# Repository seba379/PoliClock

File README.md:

# PoliClock

**Orologio da scrivania alimentato via USB, integrato nel volto di una poliziotta chibi stampata in 3D.**

> Stato: **specifiche preliminari (v0.6), schema e PCB KiCad rev 0.2 in bozza, non validati né ordinati** · Aggiornamento: 2026-11-08\
> Lingua progetto: italiano · Documentazione in Markdown · Hardware non ancora acquistato né validato.

## Il prodotto

PoliClock è un regalo personalizzato: una statuetta simpatica e stilizzata di una poliziotta, con un display **circolare integrato al posto del volto**. Durante il giorno il quadrante visualizza **ora, data, temperatura ambiente e umidità relativa**; di notte si spegne. È alimentato in continuo da un **cavo USB-C** collegato al retro della base d'appoggio, che contiene la scheda (`DEC-048`); nella V1 non c'è batteria.

La modalità scelta è **ibrida**: quadrante normalmente attenuato ma leggibile; la pressione di un pulsante attiva temporaneamente la luminosità elevata. La priorità è la qualità estetica senza sacrificare sicurezza, affidabilità e manutenzione.

## Decisioni già confermate

- Statuetta **poliziotta chibi**, volutamente sproporzionata, da stampare in 3D.
- Display **rotondo**, montato a filo/in incasso al posto del viso; non esterno o incollato.
- Schermata V1: **ora, data, temperatura e umidità**; niente funzioni domotiche o statistiche richieste.
- **Nessuna batteria nella V1**: alimentazione continua da **cavo USB-C** sulla parte posteriore bassa, sul retro della base d'appoggio che contiene la scheda (`DEC-048`). Eventuale batteria rimandata a versioni future.
- Schermo **attenuato in condizioni normali**, più luminoso dopo un'interazione.
- **Di notte il display è spento** (default 23:00–07:00, configurabile).
- Aspetto con **uniforme blu e cappello**.
- **Nessun Wi-Fi/NTP nella V1**: l'ora si imposta offline.
- Elettronica su **PCB custom** (KiCad, prodotto e assemblato da JLCPCB): scheda principale separata dal display, collegata via cavo.
- Strumenti: **KiCad 10**, **VS Code + ESP-IDF**, **Blender** e CAD a codice (build123d).
- Display **IPS rotondo 1,28"** (240×240, GC9A01) e interazione con un **pulsante** fisico; display su **modulo a 7 pin** provabile su breadboard, senza touch (`DEC-034`).
- Impostazioni (ora, fascia notte) da un **configuratore su PC** collegato via USB.

## Architettura candidata, NON ancora congelata

- **Scheda principale** rettangolare (busto/base preferito, posizione da confermare con il CAD): modulo **ESP32-C3-WROOM-02-N4** (`DEC-044`), protezioni USB, regolatore 3,3 V, USB-C, connettori.
- **RTC esterno** su modulo Adafruit DS3231 STEMMA QT con pila CR1220, collegato via cavo: l'ora resta salva a cavo scollegato.
- **Modulo display** GC9A01 nella testa, collegato alla scheda principale con un cavetto a 7 fili attraverso il collo.
- Sensore T/RH: **Sensirion SHT40** su modulo breakout commerciale, in vano ventilato, collegato con 4 fili.
- Prima del PCB: **prototipo su banco** con moduli commerciali per validare display su cavo, consumi e firmware.
- Firmware **ESP-IDF**.

**Importante:** consumi, temperature interne e ingombri vanno misurati sul prototipo prima di consolidare la BOM.

| Concept del prodotto | Schema a blocchi |
|---|---|
|  |  |

Le immagini sono **illustrative** (vedi [assets](assets/README.md)).

## Documentazione

| Documento | Contenuto |
|---|---|
| [Visione e perimetro](docs/00-visione-perimetro.md) | Scopo, utenti, esclusioni, vincoli |
| [Requisiti di prodotto](docs/01-requisiti-prodotto.md) | Requisiti identificati, criteri di accettazione |
| [Architettura hardware](docs/02-architettura-hardware.md) | Moduli, collegamenti, selezione candidata |
| [Alimentazione](docs/03-alimentazione-ricarica.md) | USB-C, regolatore, tampone RTC, consumi e calore |
| [Specifiche firmware](docs/04-specifiche-firmware.md) | Componenti, stati, timekeeping, errori |
| [UI/UX](docs/05-interfaccia-utente.md) | Layout, luminosità, interazione, messaggi |
| [Progettazione meccanica](docs/06-progettazione-meccanica.md) | Testa, corpo, base con zavorra, stampa 3D |
| [Verifiche e test](docs/07-piano-verifica.md) | Prove funzionali, elettriche e meccaniche |
| [BOM preliminare](docs/08-bom-preliminare.md) | Acquisti, alternative e controlli pre-ordine |
| [Roadmap](docs/09-roadmap.md) | Milestone, deliverable, gate |
| [Decisioni e questioni aperte](docs/10-decisioni-aperte.md) | Decision log e dubbi tecnici |
| [Fonti](docs/11-fonti.md) | Documenti ufficiali e risorse tecniche |
| [Selezione componenti](docs/12-selezione-componenti.md) | Componenti dello schema, codici LCSC, assegnazione GPIO |
| [Preventivo JLCPCB](docs/13-ordine-jlcpcb.md) | File da caricare, opzioni PCB e montaggio, controlli DFM, parti da saldare a mano |
| [Hardware KiCad](hardware/README.md) | Progetti KiCad, PDF, BOM JLCPCB, rigenerazione |

## Organizzazione di lavoro prevista

```text
PoliClock/
├── README.md
├── docs/                  # specifiche e verifiche
├── assets/                # concept, render, modelli di riferimento futuri
├── firmware/              # progetto ESP-IDF da avviare in M1/M4
├── hardware/              # progetto KiCad scheda principale rev 0.2 (bozza), BOM/CPL JLCPCB (M2)
├── tools/                 # configuratore da PC via USB (M4)
└── mechanical/            # Blender (chibi), build123d (parti tecniche), STL/3MF
```

Le directory `firmware/`, `tools/` e `mechanical/` sono **previste**, non ancora presenti: non si pubblicano file placeholder che possano essere scambiati per firmware o modelli funzionanti.

## Convenzioni

- **CONF**: decisione espressamente confermata dall'utente.
- **CAND**: soluzione tecnica candidata, soggetta a verifica.
- **TGT**: obiettivo di progetto non ancora validato.
- **TBD**: scelta/misura ancora da definire.
- Ogni requisito ha un ID stabile (es. `PR-FUN-001`) e uno o più test di accettazione (`VT-...`).
- Nessun dato prestazionale ipotetico va descritto come misurato.

## Primo passo operativo

Milestone M1 della [roadmap](docs/09-roadmap.md): scegliere sui datasheet MCU, RTC e regolatore, montare il **prototipo su banco** con moduli commerciali, provare il display su cavo e misurare i consumi **prima** di disegnare il PCB e il CAD.

## Avvertenze

Progetto hobbistico per un regalo personale, non prodotto certificato per vendita. L'alimentazione continua da USB richiede comunque protezione dell'ingresso, fissaggio dei connettori e verifica termica a scocca chiusa. L'estetica richiama una poliziotta, senza implicare affiliazione o approvazione ufficiale della Polizia di Stato.

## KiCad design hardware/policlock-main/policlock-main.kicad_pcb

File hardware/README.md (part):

# Hardware PoliClock (KiCad 10)

**Stato (rev 0.2, 2026-11-08):** schema e PCB della scheda principale **in bozza**, rifatti dopo la revisione tecnica indipendente (esito sulla rev 0.1: *NOT APPROVED FOR FABRICATION*; stato dei rilievi in [docs/10](../docs/10-decisioni-aperte.md) §6).

**Correzioni del 2026-11-08, ramo `codex/pcb-edge-courtyard-fixes`:** C7 spostato a 2,60 mm dal bordo; courtyard/F.Fab di J2–J5 completati; FID1 spostato di 1,5 mm con la sua zona di rispetto. Commit autorizzato dal proprietario; ERC/DRC e confronto riportati nella [nota delle modifiche](../docs/revisioni/2026-11-08/correzioni/README.md). Vista 2D dei courtyard: [pcb-courtyard.svg](../docs/revisioni/2026-11-08/correzioni/pcb-courtyard.svg).

**Chiusura dei rilievi residui (2026-11-08, [verifica](../docs/revisioni/2026-11-08/verifica-claude.md)):**

- C1 portato a **1 µF** (C15849) e C2 a **4,7 µF** (C19666, Basic): restano 5,7 µF nominali su VBUS (`DEC-042`).
- Cartigli portati a rev 0.2 e annotazioni dello schema corrette.
- `esporta.py` ora si ferma se ERC, DRC o il controllo meccanico falliscono.
- PDF, BOM, layout e render 3D sono rigenerati.

**Pin BUSY su J2 (`DEC-049`, 2026-11-09):**

- J2 diventa un header **1×8** (`PinHeader_1x08_P2.54mm_Horizontal`, simbolo `PoliClock:PinHeader_1x08_P2.54_THT`): pin 1–7 invariati, **pin 8 = BUSY** per un eventuale e-paper.
- Il pin 8 va a IO1 attraverso R23 1 kΩ (C21190, Basic); TP10 resta su IO1. Il pull-down interno lo abilita il firmware.
- J2 si sposta di 2,54 mm a sinistra: con il pin 1 fermo, il pin 8 cadrebbe sotto U3.
- Modifica con `scripts/dec049_schema.py` e `scripts/dec049_pcb.py`, poi `sbroglia_main.py --conserva` e `cucitura_gnd.py`.
- ERC 0, DRC 0/0/0 con parità, controllo meccanico PASS.
- Verifica di IO0/IO1 sui datasheet Espressif in [docs/10](../docs/10-decisioni-aperte.md) §16.
- Dopo la terza revisione (R3-001, R3-003): 8 vie GND in più (4 accanto alla EPAD di U3, 1 vicino al pin 9, 3 nell'isola del retro della zona J2/passivi), aggiunte a mano; DRC 0/0/0. Dettagli in [docs/10](../docs/10-decisioni-aperte.md) §17.

**Contorno rettangolare 50,5 × 41,5 mm (`DEC-045`, 2026-11-08):** niente intaglio, antenna di U3 sulla scheda con zona vietata, corpo di tutte le parti montate da JLC a ≥ 2,5 mm da ogni bordo tranne J1 (unica eccezione DFM). Modifica con `scripts/dec045_pcb.py`. ERC 0, DRC 0/0/0, controllo meccanico PASS (margine minimo 2,99 mm). Dettagli in [docs/10](../docs/10-decisioni-aperte.md) §12.

**Modulo ESP32-C3-WROOM-02-N4 (`DEC-044`, 2026-11-08):** sostituisce il MINI-1-H4X (a JLC solo "Standard"). Impronta di progetto `PoliClock:ESP32-C3-WROOM-02` (derivata da quella di KiCad, EPAD senza vie dopo `DEC-046`, niente serigrafia sopra l'antenna), intaglio allargato a 8,5 × 20,2 mm, coppia USB ridisegnata sui pin 13/14, sbroglio rifatto, cucitura GND, R16 10 k + C11 10 nF (FIN-003), serigrafia a 1,0 mm (FIN-005), regola PTH in `.kicad_dru` (FIN-007), script Gerber bloccato (FIN-006). ERC 0, DRC 0/0/0 con parità, controllo meccanico PASS. Dettagli in [docs/10](../docs/10-decisioni-aperte.md) §11.

**Connettori a foro passante (`DEC-043`, 2026-11-08):** J2 (header 1×7 2,54 mm, 1×8 dal `DEC-049`) e J3/J4/J5 (JST PH B4B-PH-K-S) sono a foro passante e **saldati a mano dal proprietario**, come le 4 linguette del guscio di J1 (`DEC-047`); JLC monta tutto il resto, J1 compreso. Le impronte vengono dalla libreria standard di KiCad 10. J2–J5 hanno il campo `Montaggio` = "a mano, parte del proprietario" e l'attributo "escluso dai file di posizionamento": non compaiono in BOM JLC e CPL, ma sono nella BOM completa. Modifica con `scripts/dec043_connettori_tht.py`, poi sbroglio delle sole connessioni mancanti con `scripts/sbroglia_main.py --conserva`. ERC 0, DRC 0/0/0 con parità, controllo meccanico PASS. Dettagli in [docs/10](../docs/10-decisioni-aperte.md) §10.

- **Report salvati**: ERC e DRC rieseguiti con `kicad-cli` sulla rev 0.2 (`policlock-main/erc.rpt`, `drc.rpt`). Sono verifiche automatiche del progetto.
- **Test eseguiti sull'hardware**: nessuno. Tutti i test del [piano di verifica](../docs/07-piano-verifica.md) sono NOT_RUN.
- **Non ordinare**: prima servono studio volumetrico 1:1 (`OPEN-028`), verifica del modulo display ricevuto (`OPEN-016`), prototipo M1 e DFM JLC. La revisione visiva del proprietario in KiCad è stata fatta il 2026-11-08 con esito positivo (`OPEN-027` chiusa) e ripetuta sul layout finale `09200dc` (`OPEN-030` chiusa).

## Struttura

| Cartella | Contenuto |
|---|---|
| `policlock-main/` | Scheda principale: schema gerarchico (USB e alimentazione, MCU, display a 7 pin, periferiche I²C e pulsante), PCB 50,5 × 41,5 mm, PDF, BOM e CPL per JLCPCB, render, STEP della sagoma, report ERC/DRC |
| `lib/` | Libreria di progetto `PoliClock` (simboli e footprint delle parti specifiche) |
| `scripts/` | Generatori di schema e PCB, sbroglio con Freerouting, esportazioni |

È l'**unico PCB custom**: display, sensore SHT40 e RTC sono moduli commerciali collegati con cavetti (`DEC-024`, `DEC-028`, `DEC-034`).

Ogni componente montato da JLC ha il campo **`LCSC`** (codice JLCPCB/LCSC); J2–J5 non hanno codice LCSC e portano il campo **`Montaggio`** = "a mano, parte del proprietario" (`DEC-043`). Simboli e footprint di passivi, SOT, USBLC6, TLV75533 e AO3401A vengono dalle librerie standard di KiCad 10; la USB-C usa il footprint KiCad ricavato dal disegno HRO (copiato nella libreria di progetto con la serigrafia frontale tolta); anche i connettori a foro passante J2–J5 usano impronte standard (`Connector_PinHeader_2.54mm`, `Connector_JST`); le altre parti vengono dalla libreria `PoliClock`.

## PCB della scheda principale

- `policlock-main/policlock-main.kicad_pcb`: **50,5 × 41,5 mm, 2 strati, 1,6 mm, componenti solo sopra** (`DEC-030`, `DEC-045`). L'antenna del modulo ESP32 sta sulla scheda, verso il bordo destro, sopra una zona vietata senza rame su entrambi gli strati (niente intaglio). Piani GND su entrambi gli strati. Nessun tasto: reset e boot dai punti di test TP6 (EN) e TP11 (IO9) sul retro (`DEC-039`). Tre fiducial da 1 mm sul lato componenti. Dettagli in [docs/02](../docs/02-architettura-hardware.md) §3.2.
- **Regole JLCPCB** (vincolo `SC-008`, `DEC-040`; pagine ufficiali consultate il 2026-11-08, da ricontrollare all'ordine):
  - fabbricazione 2 strati: distanza 0,15 mm, pista ≥ 0,15 mm (alimentazioni 0,3–0,4 mm), anello delle piazzole PTH ≥ 0,18 mm (regola `.kicad_dru`), testi della serigrafia ≥ 1,0 mm, vie 0,6/0,3 mm, foro-foro ≥ 0,25 mm (JLC 0,2), foro-rame ≥ 0,3 mm (JLC 0,28), rame-bordo 0,3 mm (JLC 0,2) più una fascia di 0,45 mm senza piste lungo il contorno;
  - assemblaggio: corpo dei componenti montati da JLC ≥ 2,5 mm da ogni bordo; controllo aggiuntivo `scripts/verifica_meccanica_pcb.py`, richiamato anche dal generatore. **Unica eccezione J1** (USB-C a filo del bordo inferiore), da approvare al DFM JLC (`DEC-045`). Le parti saldate a mano (J2–J5, `DEC-043`) non hanno il margine, ma il loro courtyard è controllato; le regole di fabbricazione valgono anche per le loro piazzole. Fiducial con zona senza rame.
  - `policlock-main/policlock-main.kicad_dru`: anello PTH ≥ 0,18 mm (FIN-007) e una deroga che ignora il controllo serigrafia-bordo **solo per J2** (la serigrafia della libreria segue i piedini oltre il bordo e non viene stampata).
- Controlli DRC **riabilitati**: courtyard mancante o sovrapposto, fori nei courtyard, footprint diversi dalla libreria, serigrafia sovrapposta o fuori bordo.
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
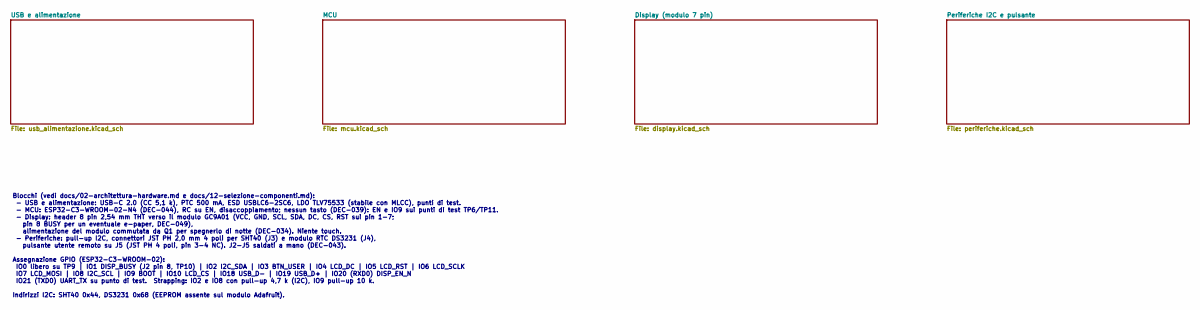
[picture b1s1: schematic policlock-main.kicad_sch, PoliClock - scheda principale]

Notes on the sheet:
Blocchi (vedi docs/02-architettura-hardware.md e docs/12-selezione-componenti.md): - USB e alimentazione: USB-C 2.0 (CC 5,1 k), PTC 500 mA, ESD USBLC6-2SC6, LDO TLV75533 (stabile con MLCC), punti di test. - MCU: ESP32-C3-WROOM-02-N4 (DEC-044), RC su EN, disaccoppiamento; nessun tasto (DEC-039): EN 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

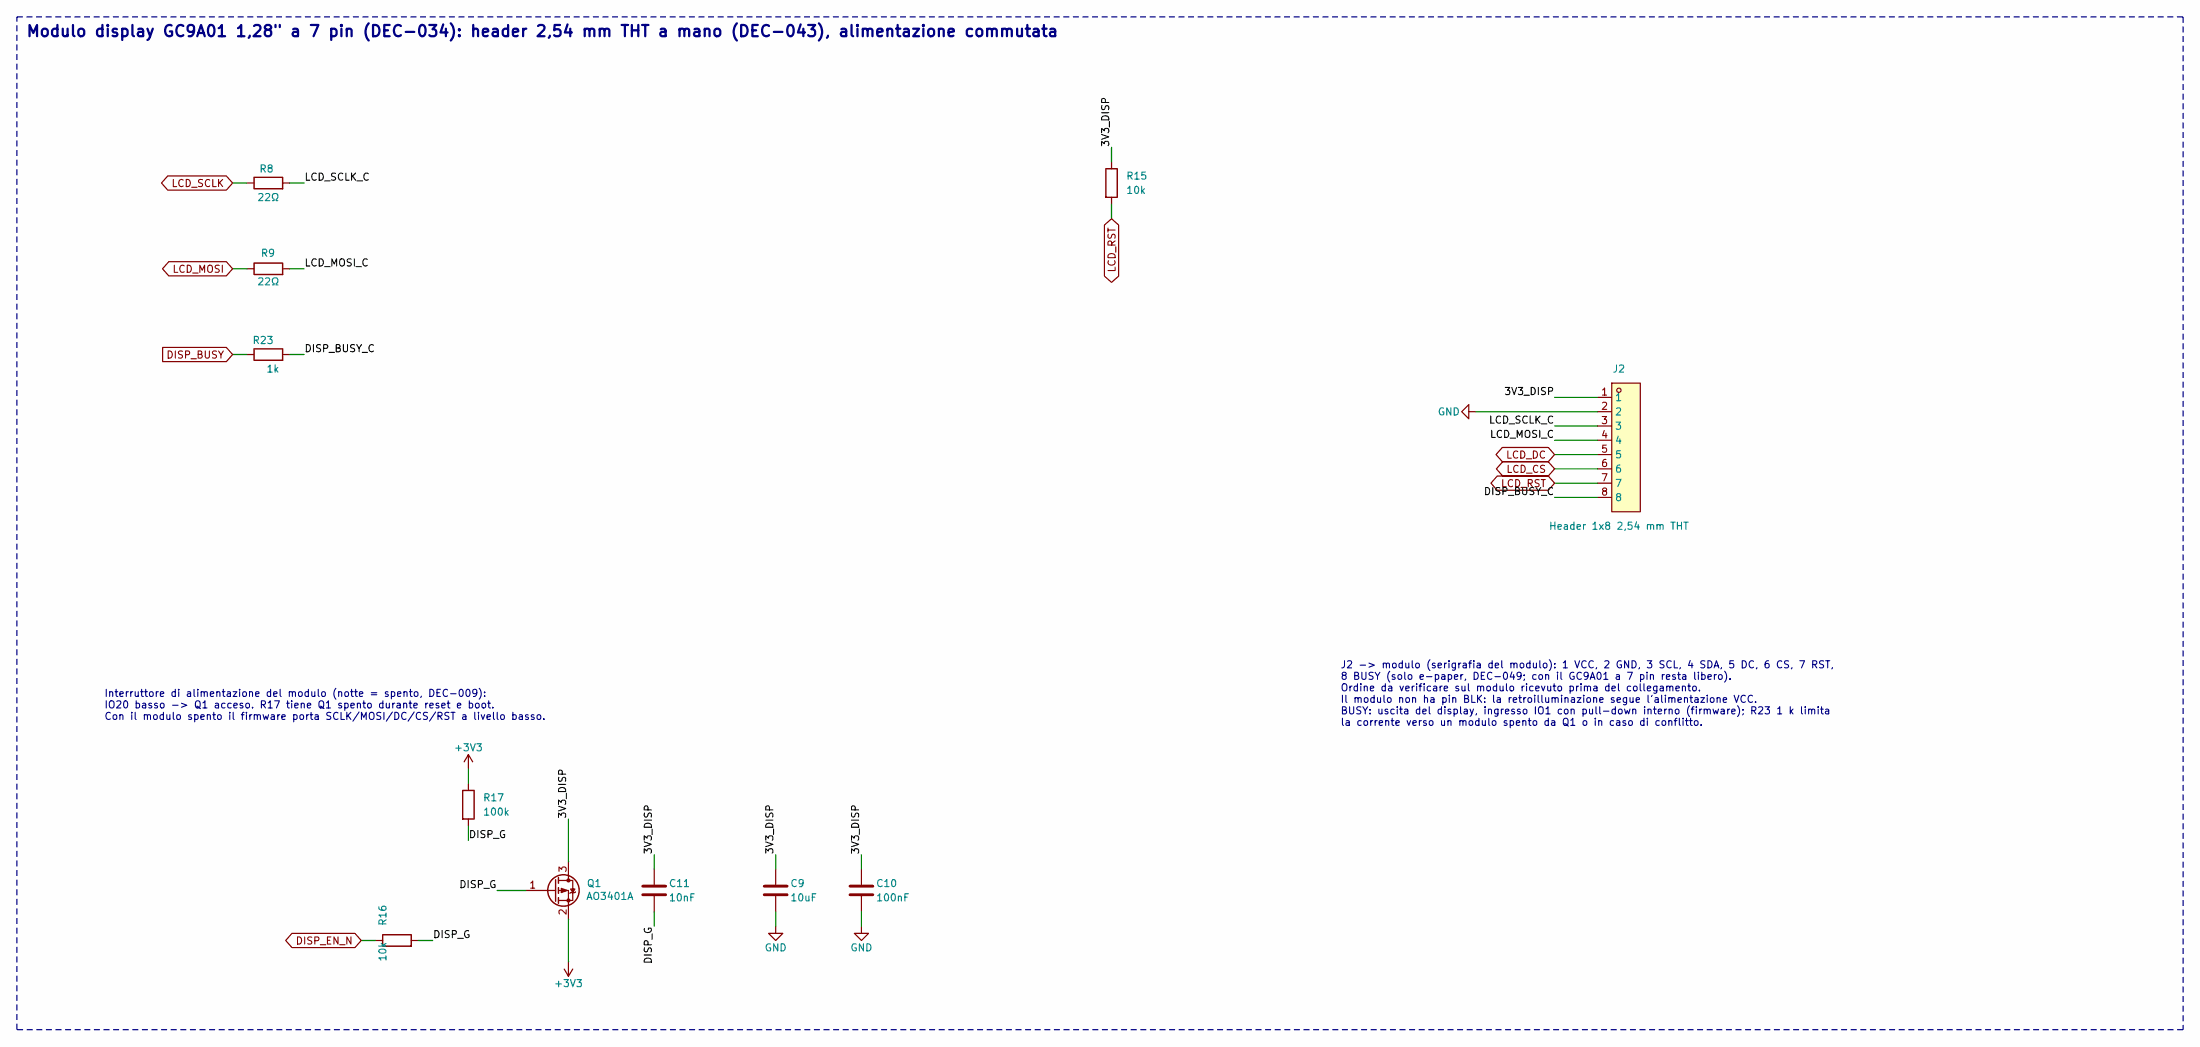
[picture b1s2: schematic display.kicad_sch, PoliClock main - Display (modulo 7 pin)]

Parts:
C9: 10uF; C_0603_1608Metric; LCSC C19702
C10: 100nF; C_0603_1608Metric; LCSC C14663
C11: 10nF; C_0603_1608Metric; LCSC C57112
J2: Header 1x8 2,54 mm THT; PinHeader_1x08_P2.54mm_Horizontal
Q1: AO3401A; SOT-23; LCSC C15127
R8, R9: 22Ω; R_0603_1608Metric; LCSC C23345
R15, R16: 10k; R_0603_1608Metric; LCSC C25804
R17: 100k; R_0603_1608Metric; LCSC C25803
R23: 1k; R_0603_1608Metric; LCSC C21190

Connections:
+3V3: Q1.2 (S), R17.1; also elsewhere on the board
/Display (modulo 7 pin)/3V3_DISP: C9.1, C10.1, C11.1, J2.1, Q1.3 (D), R15.1
/Display (modulo 7 pin)/DISP_BUSY_C: J2.8, R23.2
/Display (modulo 7 pin)/DISP_G: C11.2, Q1.1 (G), R16.2, R17.2
/Display (modulo 7 pin)/LCD_MOSI_C: J2.4, R9.2
/Display (modulo 7 pin)/LCD_SCLK_C: J2.3, R8.2
DISP_BUSY: R23.1; also elsewhere on the board
DISP_EN_N: R16.1; also elsewhere on the board
GND: C9.2, C10.2, J2.2; also elsewhere on the board
LCD_CS: J2.6; also elsewhere on the board
LCD_DC: J2.5; also elsewhere on the board
LCD_MOSI: R9.1; also elsewhere on the board
LCD_RST: J2.7, R15.2; also elsewhere on the board
LCD_SCLK: R8.1; also elsewhere on the board

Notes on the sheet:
Modulo display GC9A01 1,28" a 7 pin (DEC-034): header 2,54 mm THT a mano (DEC-043), alimentazione commutata
Interruttore di alimentazione del modulo (notte = spento, DEC-009): IO20 basso -> Q1 acceso. R17 tiene Q1 spento durante reset e boot. Con il modulo spento il firmware porta SCLK/MOSI/DC/CS/RST a livello basso.
J2 -> modulo (serigrafia del modulo): 1 VCC, 2 GND, 3 SCL, 4 SDA, 5 DC, 6 CS, 7 RST, 8 BUSY (solo e-paper, DEC-049; con il GC9A01 a 7 pin resta libero). Ordine da verificare sul modulo ricevuto prima del collegamento. Il modulo non ha pin BLK: la retroilluminazione segue l'alimentazione VCC. BUSY: 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

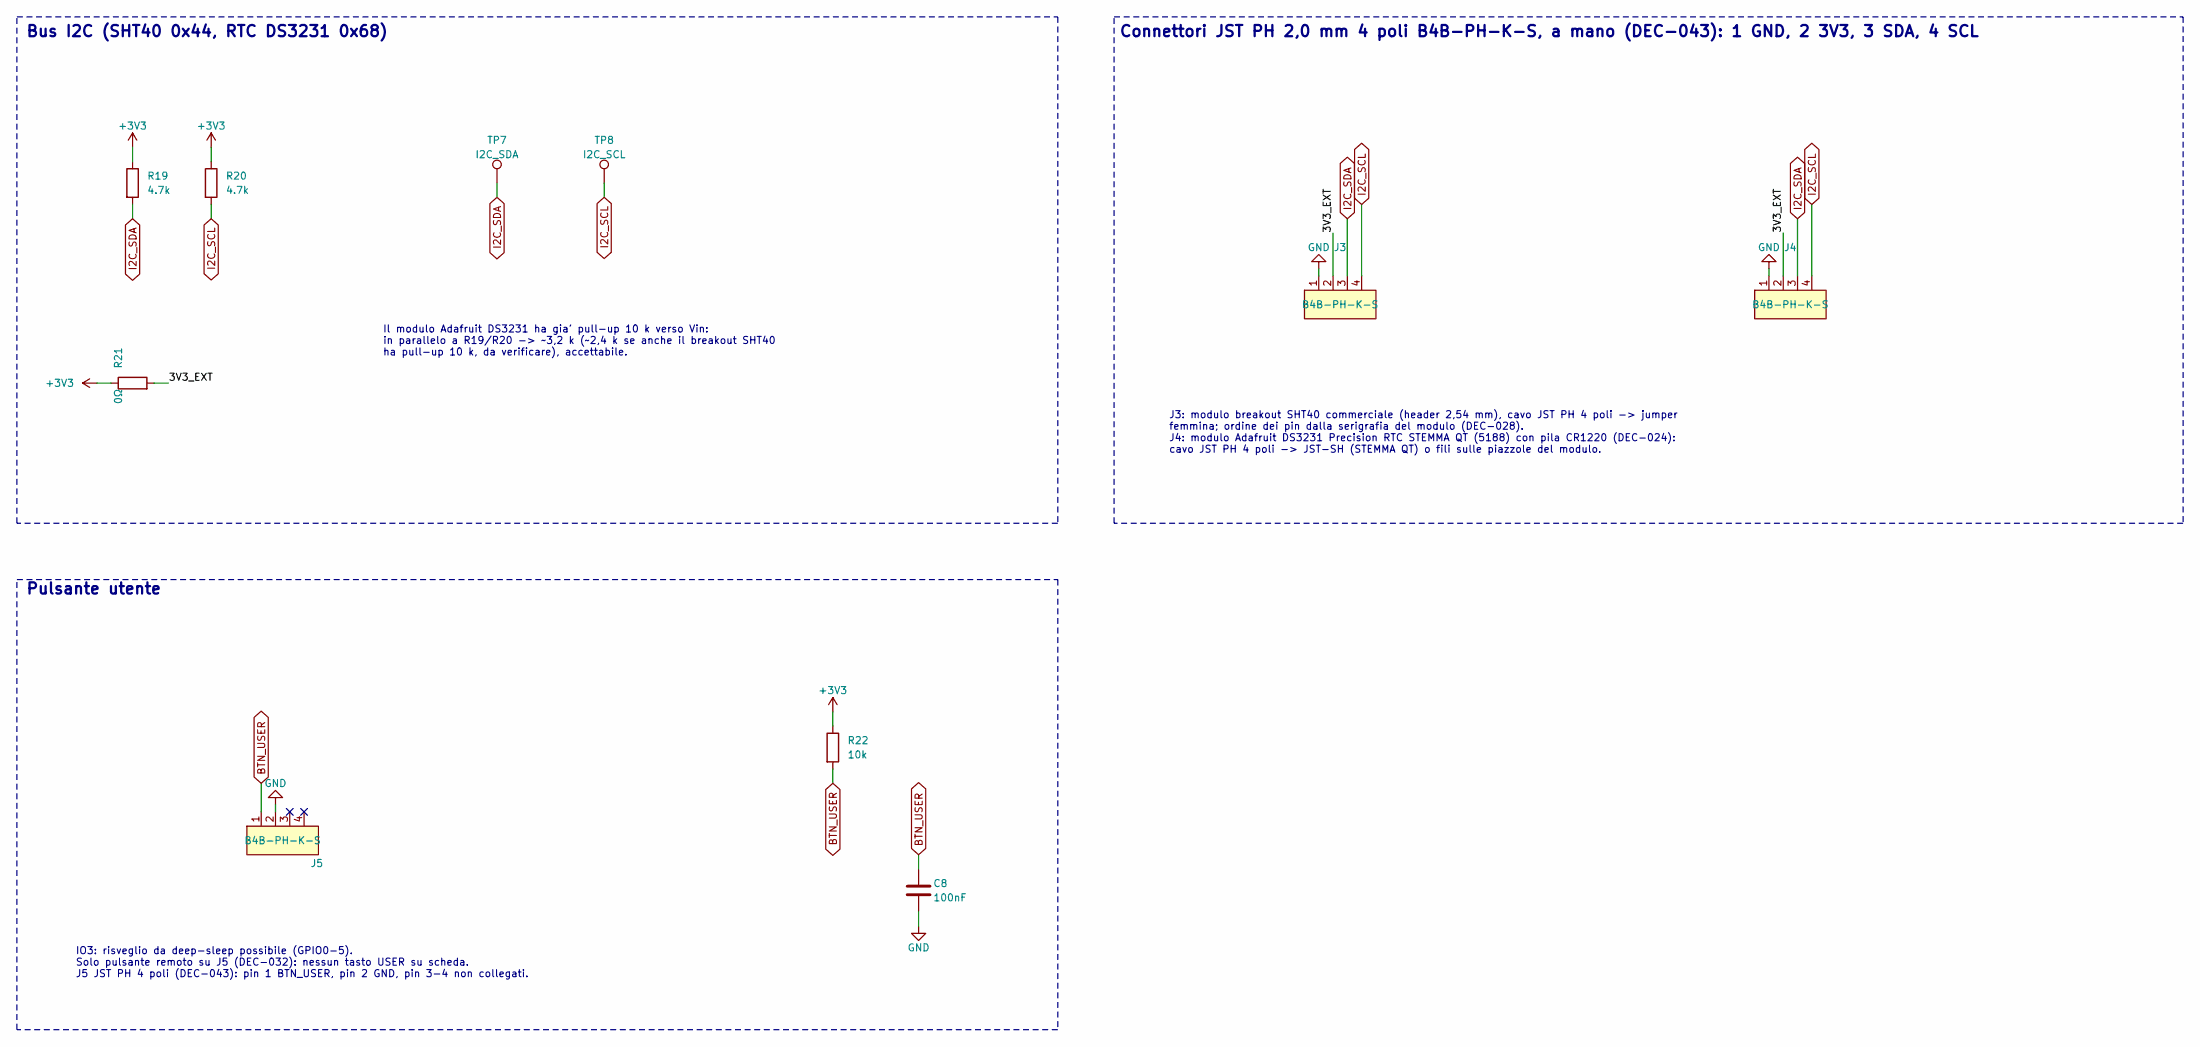
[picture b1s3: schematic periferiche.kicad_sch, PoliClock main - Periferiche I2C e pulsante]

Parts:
C8: 100nF; C_0603_1608Metric; LCSC C14663
J3, J4, J5: B4B-PH-K-S; JST_PH_B4B-PH-K_1x04_P2.00mm_Vertical
R19, R20: 4.7k; R_0603_1608Metric; LCSC C23162
R21: 0Ω; R_0603_1608Metric; LCSC C21189
R22: 10k; R_0603_1608Metric; LCSC C25804
TP7: I2C_SDA; TestPoint_Pad_D1.5mm
TP8: I2C_SCL; TestPoint_Pad_D1.5mm

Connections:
+3V3: R19.1, R20.1, R21.1, R22.1; also elsewhere on the board
/Periferiche I2C e pulsante/3V3_EXT: J3.2, J4.2, R21.2
BTN_USER: C8.1, J5.1, R22.2; also elsewhere on the board
GND: C8.2, J3.1, J4.1, J5.2; also elsewhere on the board
I2C_SCL: J3.4, J4.4, R20.2, TP8.1; also elsewhere on the board
I2C_SDA: J3.3, J4.3, R19.2, TP7.1; also elsewhere on the board

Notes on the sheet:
Il modulo Adafruit DS3231 ha gia' pull-up 10 k verso Vin: in parallelo a R19/R20 -> ~3,2 k (~2,4 k se anche il breakout SHT40 ha pull-up 10 k, da verificare), accettabile.
Connettori JST PH 2,0 mm 4 poli B4B-PH-K-S, a mano (DEC-043): 1 GND, 2 3V3, 3 SDA, 4 SCL
J3: modulo breakout SHT40 commerciale (header 2,54 mm), cavo JST PH 4 poli -> jumper femmina; ordine dei pin dalla serigrafia del modulo (DEC-028). J4: modulo Adafruit DS3231 Precision RTC STEMMA QT (5188) con pila CR1220 (DEC-024): cavo JST PH 4 poli -> JST-SH (STEMMA QT) o fili sulle piazzole del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
IO3: risveglio da deep-sleep possibile (GPIO0-5). Solo pulsante remoto su J5 (DEC-032): nessun tasto USER su scheda. J5 JST PH 4 poli (DEC-043): pin 1 BTN_USER, pin 2 GND, pin 3-4 non collegati.
Bus I2C (SHT40 0x44, RTC DS3231 0x68)
Pulsante utente

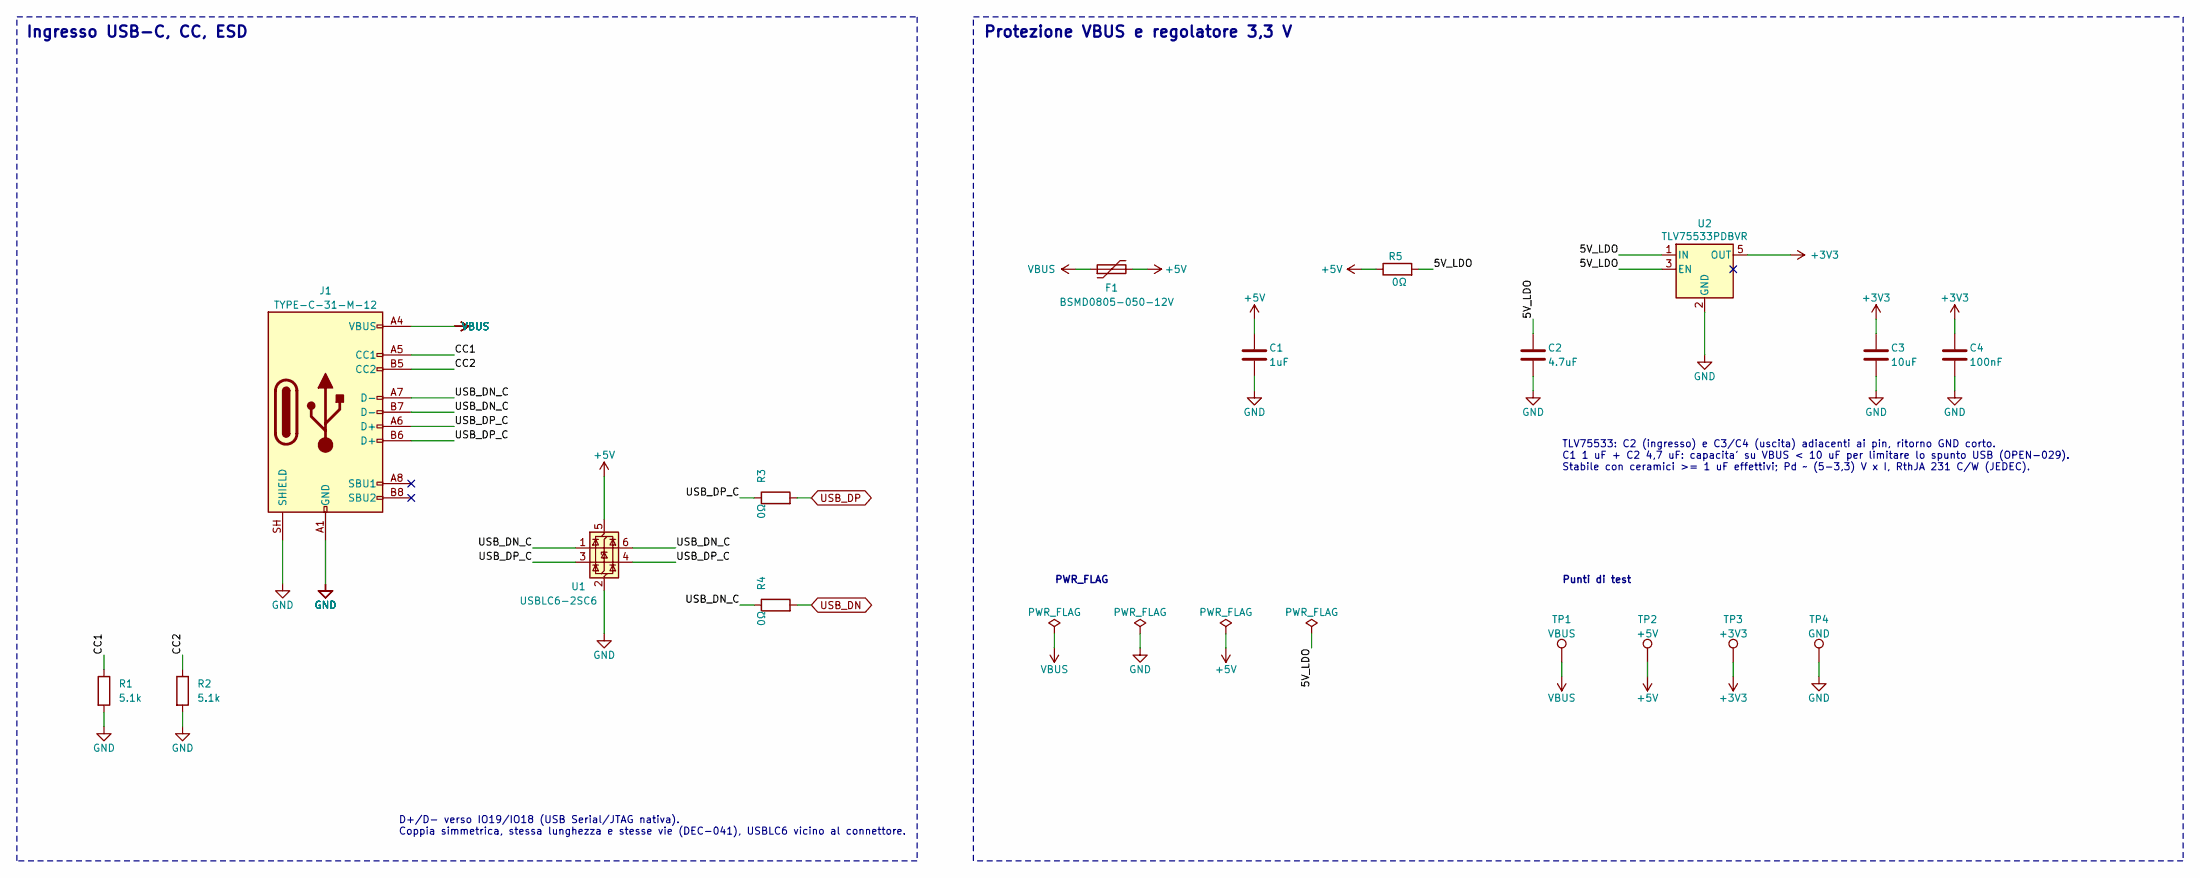
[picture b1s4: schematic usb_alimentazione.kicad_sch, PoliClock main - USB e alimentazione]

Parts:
C1: 1uF; C_0603_1608Metric; LCSC C15849
C2: 4.7uF; C_0603_1608Metric; LCSC C19666
C3: 10uF; C_0603_1608Metric; LCSC C19702
C4: 100nF; C_0603_1608Metric; LCSC C14663
F1: BSMD0805-050-12V; Fuse_0805_2012Metric; LCSC C2977522
J1: TYPE-C-31-M-12; USB_C_Receptacle_HRO_TYPE-C-31-M-12; LCSC C165948
R1, R2: 5.1k; R_0603_1608Metric; LCSC C23186
R3, R4, R5: 0Ω; R_0603_1608Metric; LCSC C21189
TP1: VBUS; TestPoint_Pad_D1.5mm
TP2: +5V; TestPoint_Pad_D1.5mm
TP3: +3V3; TestPoint_Pad_D1.5mm
TP4: GND; TestPoint_Pad_D1.5mm
U1: USBLC6-2SC6; SOT-23-6; LCSC C7519
U2: TLV75533PDBVR; SOT-23-5; LCSC C404027

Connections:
+3V3: C3.1, C4.1, TP3.1, U2.5 (OUT); also elsewhere on the board
+5V: C1.1, F1.2, R5.1, TP2.1, U1.5 (VBUS)
/USB e alimentazione/5V_LDO: C2.1, R5.2, U2.1 (IN), U2.3 (EN)
/USB e alimentazione/CC1: J1.A5 (CC1), R1.1
/USB e alimentazione/CC2: J1.B5 (CC2), R2.1
/USB e alimentazione/USB_DN_C: J1.A7 (D-), J1.B7 (D-), R4.1, U1.1 (I/O1), U1.6 (I/O1)
/USB e alimentazione/USB_DP_C: J1.A6 (D+), J1.B6 (D+), R3.1, U1.3 (I/O2), U1.4 (I/O2)
GND: C1.2, C2.2, C3.2, C4.2, J1.A1 (GND), J1.A12 (GND), J1.B1 (GND), J1.B12 (GND), J1.SH (SHIELD), R1.2, R2.2, TP4.1, U1.2 (GND), U2.2 (GND); also elsewhere on the board
USB_DN: R4.2; also elsewhere on the board
USB_DP: R3.2; also elsewhere on the board
VBUS: F1.1, J1.A4 (VBUS), J1.A9 (VBUS), J1.B4 (VBUS), J1.B9 (VBUS), TP1.1

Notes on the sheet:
Ingresso USB-C, CC, ESD
PWR_FLAG
D+/D- verso IO19/IO18 (USB Serial/JTAG nativa). Coppia simmetrica, stessa lunghezza e stesse vie (DEC-041), USBLC6 vicino al connettore.
TLV75533: C2 (ingresso) e C3/C4 (uscita) adiacenti ai pin, ritorno GND corto. C1 1 uF + C2 4,7 uF: capacita' su VBUS < 10 uF per limitare lo spunto USB (OPEN-029). Stabile con ceramici >= 1 uF effettivi; Pd ~ (5-3,3) V x I, RthJA 231 C/W (JEDEC).
Protezione VBUS e regolatore 3,3 V
Punti di test

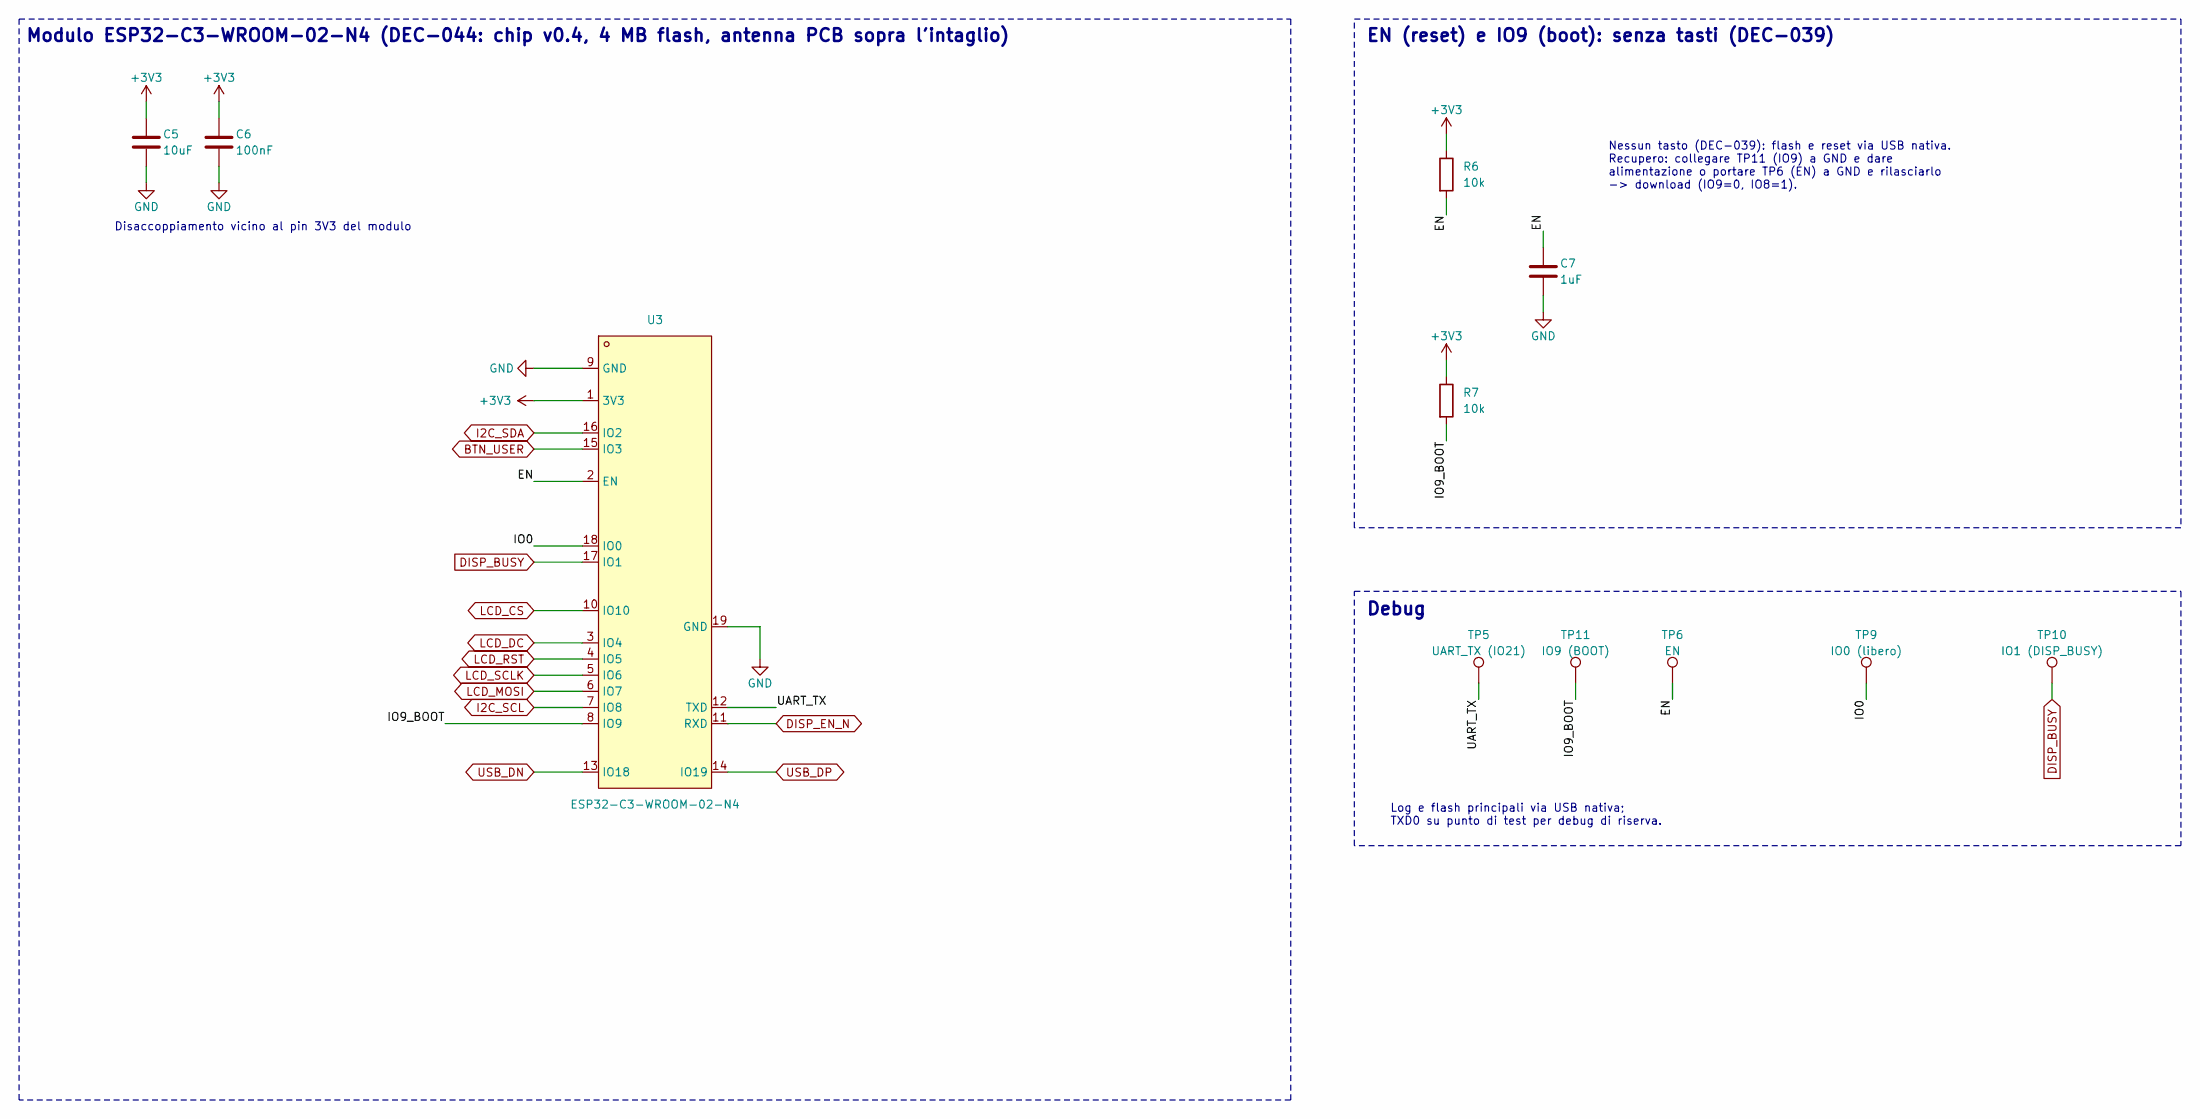
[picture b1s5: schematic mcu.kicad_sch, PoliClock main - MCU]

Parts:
C5: 10uF; C_0603_1608Metric; LCSC C19702
C6: 100nF; C_0603_1608Metric; LCSC C14663
C7: 1uF; C_0603_1608Metric; LCSC C15849
R6, R7: 10k; R_0603_1608Metric; LCSC C25804
TP5: UART_TX (IO21); TestPoint_Pad_D1.5mm
TP6: EN; TestPoint_Pad_D1.5mm
TP9: IO0 (libero); TestPoint_Pad_D1.5mm
TP10: IO1 (DISP_BUSY); TestPoint_Pad_D1.5mm
TP11: IO9 (BOOT); TestPoint_Pad_D1.5mm
U3: ESP32-C3-WROOM-02-N4; ESP32-C3-WROOM-02; LCSC C2934560

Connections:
+3V3: C5.1, C6.1, R6.1, R7.1, U3.1 (3V3); also elsewhere on the board
/MCU/EN: C7.1, R6.2, TP6.1, U3.2 (EN)
/MCU/IO0: TP9.1, U3.18 (IO0)
/MCU/IO9_BOOT: R7.2, TP11.1, U3.8 (IO9)
/MCU/UART_TX: TP5.1, U3.12 (TXD)
BTN_USER: U3.15 (IO3); also elsewhere on the board
DISP_BUSY: TP10.1, U3.17 (IO1); also elsewhere on the board
DISP_EN_N: U3.11 (RXD); also elsewhere on the board
GND: C5.2, C6.2, C7.2, U3.9 (GND), U3.19 (GND); also elsewhere on the board
I2C_SCL: U3.7 (IO8); also elsewhere on the board
I2C_SDA: U3.16 (IO2); also elsewhere on the board
LCD_CS: U3.10 (IO10); also elsewhere on the board
LCD_DC: U3.3 (IO4); also elsewhere on the board
LCD_MOSI: U3.6 (IO7); also elsewhere on the board
LCD_RST: U3.4 (IO5); also elsewhere on the board
LCD_SCLK: U3.5 (IO6); also elsewhere on the board
USB_DN: U3.13 (IO18); also elsewhere on the board
USB_DP: U3.14 (IO19); also elsewhere on the board

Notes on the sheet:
Disaccoppiamento vicino al pin 3V3 del modulo
EN (reset) e IO9 (boot): senza tasti (DEC-039)
Modulo ESP32-C3-WROOM-02-N4 (DEC-044: chip v0.4, 4 MB flash, antenna PCB sopra l'intaglio)
Nessun tasto (DEC-039): flash e reset via USB nativa. Recupero: collegare TP11 (IO9) a GND e dare alimentazione o portare TP6 (EN) a GND e rilasciarlo -> download (IO9=0, IO8=1).
Debug
Log e flash principali via USB nativa; TXD0 su punto di test per debug di riserva.

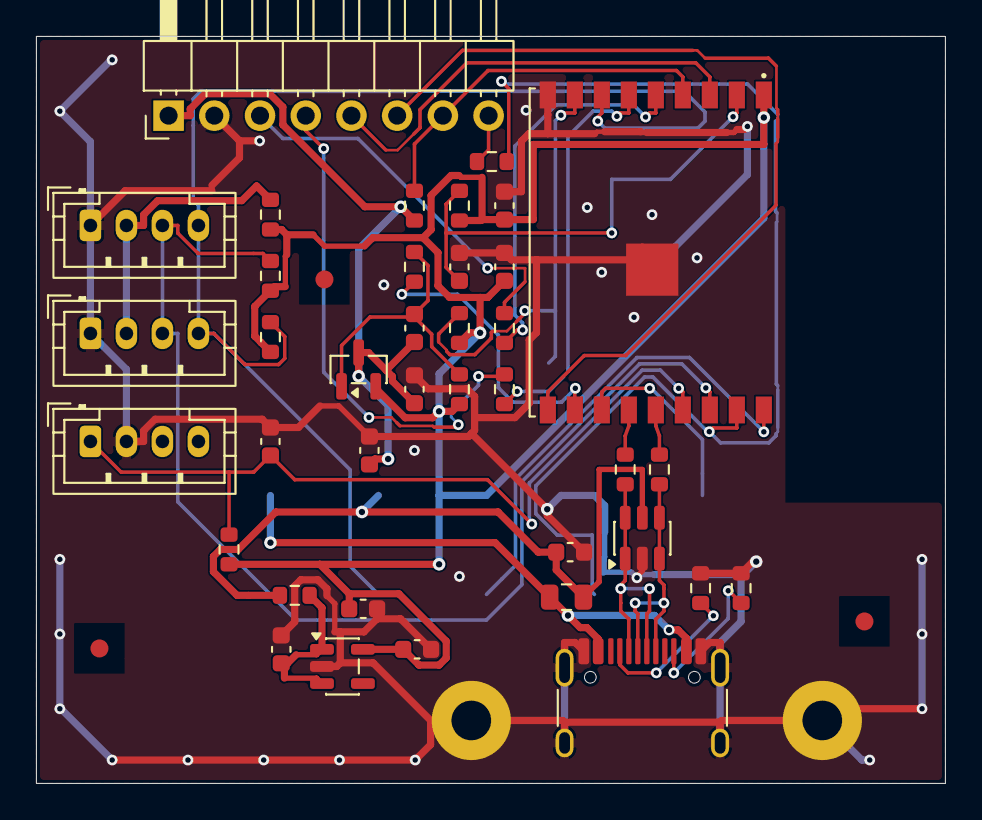
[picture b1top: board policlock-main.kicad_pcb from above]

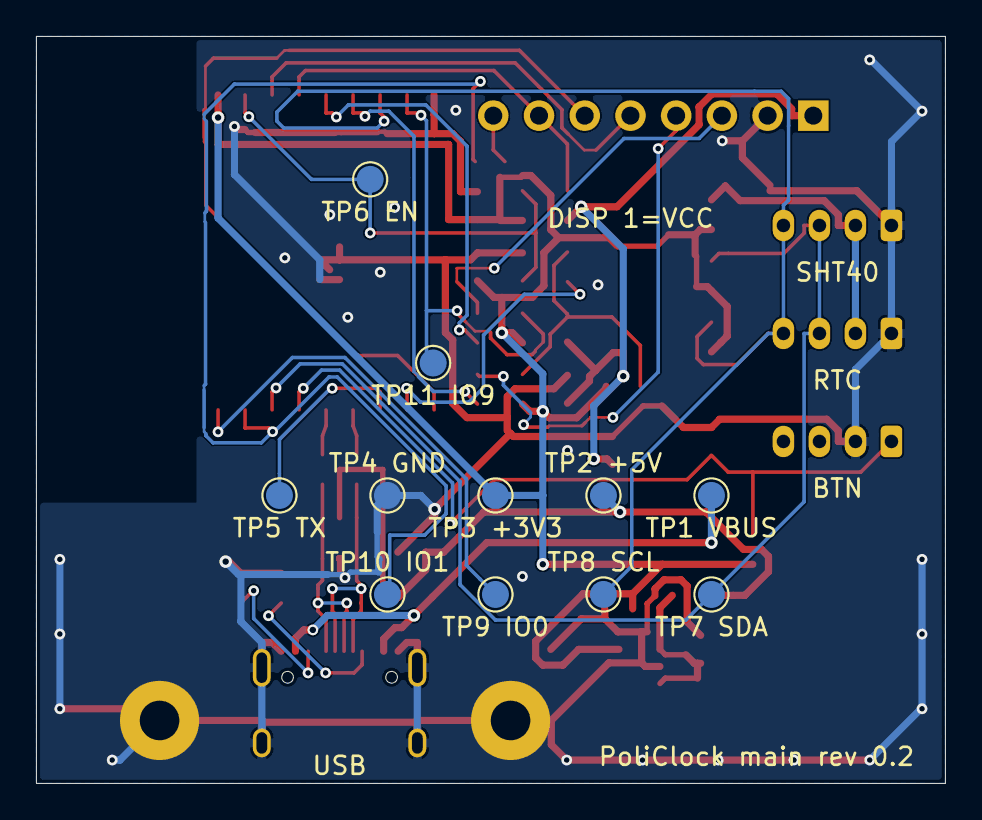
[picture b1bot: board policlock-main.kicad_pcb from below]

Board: 2 copper layers, 50.5 x 41.5 mm, 54 parts (11 on the bottom side), 31 nets.

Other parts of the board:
FID1, FID2, FID3: Fiducial; Fiducial_1mm_Mask2mm
H1, H2: M2; MountingHole_2.2mm_M2_Pad

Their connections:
GND: H1.1, H2.1; also elsewhere on the board

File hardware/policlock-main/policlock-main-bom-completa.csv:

"Riferimenti","Valore","Footprint","LCSC","Qta","DNP","Montaggio","Note"
"C1,C7","1uF","Capacitor_SMD:C_0603_1608Metric","C15849","2","","JLC (PCBA)","Unpolarized capacitor"
"C2","4.7uF","Capacitor_SMD:C_0603_1608Metric","C19666","1","","JLC (PCBA)","Unpolarized capacitor"
"C3,C5,C9","10uF","Capacitor_SMD:C_0603_1608Metric","C19702","3","","JLC (PCBA)","Unpolarized capacitor"
"C4,C6,C8,C10","100nF","Capacitor_SMD:C_0603_1608Metric","C14663","4","","JLC (PCBA)","Unpolarized capacitor"
"C11","10nF","Capacitor_SMD:C_0603_1608Metric","C57112","1","","JLC (PCBA)","Gate-drain di Q1: rampa di accensione del display (FIN-003)"
"F1","BSMD0805-050-12V","Fuse:Fuse_0805_2012Metric","C2977522","1","","JLC (PCBA)","PTC BSMD0805-050-12V: hold 0,5 A / trip 1 A"
"J1","TYPE-C-31-M-12","PoliClock:USB_C_Receptacle_HRO_TYPE-C-31-M-12","C165948","1","","JLC (PCBA)","Ricettacolo USB-C 16P HRO, solo USB 2.0 (footprint libreria KiCad dal disegno HRO)"
"J2","Header 1x7 2,54 mm THT","Connector_PinHeader_2.54mm:PinHeader_1x07_P2.54mm_Horizontal","","1","","a mano, parte del proprietario","Header maschio 1x7 2,54 mm a foro passante, a 90 gradi (va bene anche diritto): cavo Dupont 7 fili verso il modulo"
"J3-J5","B4B-PH-K-S","Connector_JST:JST_PH_B4B-PH-K_1x04_P2.00mm_Vertical","","3","","a mano, parte del proprietario","JST PH 4 poli: modulo RTC DS3231,JST PH 4 poli: modulo SHT40,JST PH 4 poli: pulsante utente remoto (pin 1-2), pin 3-4 non collegati"
"Q1","AO3401A","Package_TO_SOT_SMD:SOT-23","C15127","1","","JLC (PCBA)","-4.0A Id, -30V Vds, P-Channel MOSFET, SOT-23"
"R1,R2","5.1k","Resistor_SMD:R_0603_1608Metric","C23186","2","","JLC (PCBA)","CC1 pull-down Rd 5,1 k (sink USB-C),CC2 pull-down Rd 5,1 k (sink USB-C)"
"R3-R5,R21","0Ω","Resistor_SMD:R_0603_1608Metric","C21189","4","","JLC (PCBA)","0 ohm: isola USB D+ (eventuale 22 ohm),0 ohm: isola USB D- (eventuale 22 ohm),0 ohm: isola il regolatore per il bring-up,0 ohm: isola l'alimentazione dei moduli esterni"
"R6,R7,R15,R16,R22","10k","Resistor_SMD:R_0603_1608Metric","C25804","5","","JLC (PCBA)","Pull-up pulsante (attivo basso),Pull-up reset verso l'alimentazione del modulo,Pull-up strapping IO9 (SPI boot),RC su EN (Espressif: R 10 k, C 1 uF),Resistenza di gate 10 k: con C11 rampa di accensione lenta (FIN-003)"
"R8,R9","22Ω","Resistor_SMD:R_0603_1608Metric","C23345","2","","JLC (PCBA)","Smorzamento MOSI (valore da M1),Smorzamento SCLK (valore da M1)"
"R17","100k","Resistor_SMD:R_0603_1608Metric","C25803","1","","JLC (PCBA)","Gate verso source: modulo spento di default"
"R19,R20","4.7k","Resistor_SMD:R_0603_1608Metric","C23162","2","","JLC (PCBA)","Pull-up I2C SCL (anche strapping IO8),Pull-up I2C SDA (anche strapping IO2)"
"U1","USBLC6-2SC6","Package_TO_SOT_SMD:SOT-23-6","C7519","1","","JLC (PCBA)","Very low capacitance ESD protection diode, 2 data-line, SOT-23-6"
"U2","TLV75533PDBVR","Package_TO_SOT_SMD:SOT-23-5","C404027","1","","JLC (PCBA)","LDO 500 mA, stabile con MLCC >= 1 uF (TI SBVS320D)"
"U3","ESP32-C3-WROOM-02-N4","PoliClock:ESP32-C3-WROOM-02","C2934560","1","","JLC (PCBA)","ESP32-C3-WROOM-02-N4 (DEC-044): assemblaggio JLC Economic; radio non usata in V1 (DEC-012)"

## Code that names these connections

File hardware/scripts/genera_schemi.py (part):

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Assegnazione GPIO (ESP32-C3-MINI-1):
 IO0, IO1 liberi su punti di test | IO2 I2C_SDA | IO3 BTN_USER | IO4 LCD_DC | IO5 LCD_RST | IO6 LCD_SCLK
 IO7 LCD_MOSI | IO8 I2C_SCL | IO9 BOOT | IO10 LCD_CS | IO18 USB_D- | IO19 USB_D+ | IO20 (RXD0) DISP_EN_N
 IO21 (TXD0) UART_TX su punto di test.  Strapping: IO2 e IO8 con pull-up 4,7 k (I2C), IO9 pull-up 10 k.

Indirizzi I2C: SHT40 0x44, DS3231 0x68 (EEPROM assente sul modulo Adafruit).""", 30, 90)

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s.box(270, 20, 400, 100, "EN (reset) e IO9 (boot): senza tasti (DEC-039)")
R(s, "R6", "10k", 285, 45, "+3V3", "EN", note="RC su EN (Espressif: R 10 k, C 1 uF)")
C(s, "C7", "1uF", 300, 60, "EN", "GND")
R(s, "R7", "10k", 285, 80, "+3V3", "IO9_BOOT", note="Pull-up strapping IO9 (SPI boot)")
s.text("Nessun tasto (DEC-039): flash e reset via USB nativa.\nRecupero: collegare TP11 (IO9) a GND e dare\n"
       "alimentazione o portare TP6 (EN) a GND e rilasciarlo\n-> download (IO9=0, IO8=1).", 310, 40)

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# ----------------------------------------------------------------- Periferiche
s = sheets["periferiche.kicad_sch"]
s.box(15, 20, 200, 110, "Bus I2C (SHT40 0x44, RTC DS3231 0x68)")
R(s, "R19", "4.7k", 35, 50, "+3V3", "I2C_SDA", kind2="global", note="Pull-up I2C SDA (anche strapping IO2)")
R(s, "R20", "4.7k", 50, 50, "+3V3", "I2C_SCL", kind2="global", note="Pull-up I2C SCL (anche strapping IO8)")
R(s, "R21", "0", 35, 85, "+3V3", "3V3_EXT", rot=90, note="0 ohm: isola l'alimentazione dei moduli esterni")
TP(s, "TP7", 100, 50, "I2C_SDA", "global")
TP(s, "TP8", 120, 50, "I2C_SCL", "global")
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
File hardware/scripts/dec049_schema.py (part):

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
- simbolo PoliClock:PinHeader_1x07_P2.54_THT -> PoliClock:PinHeader_1x08_P2.54_THT (pin 8 sotto il pin 7);
  J2 diventa "Header 1x8 2,54 mm THT", impronta PinHeader_1x08_P2.54mm_Horizontal; pin 1-7 invariati;
- J2 pin 8 = DISP_BUSY_C -> R23 1 kOhm in serie (C21190, Basic) -> DISP_BUSY -> IO1 (pin 17 del WROOM-02) e TP10;
  nessun pull esterno: pull-down interno di IO1 abilitato dal firmware (docs/04);
- note dello schema aggiornate.
"""
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       + f'\t\t(pin "1"\n\t\t\t(uuid "{u()}")\n\t\t)\n\t\t(pin "2"\n\t\t\t(uuid "{u()}")\n\t\t)\n'
       f'\t\t(instances\n\t\t\t(project "policlock-main"\n\t\t\t\t(path "{PATH_DISP}"\n'
       f'\t\t\t\t\t(reference "R23")\n\t\t\t\t\t(unit 1)\n\t\t\t\t)\n\t\t\t)\n\t\t)\n\t)\n')
agg = (wire(295.91, 105.41, 288.29, 105.41) + label("DISP_BUSY_C", 288.29, 105.41, 180, "right bottom")
       + wire(53.34, RY, 55.88, RY) + global_label("DISP_BUSY", 53.34, RY, 180, "right")
       + wire(63.5, RY, 66.04, RY) + label("DISP_BUSY_C", 66.04, RY, 0, "left bottom") + r23)
t = sostituisci(t, "J2 -> modulo (serigrafia del modulo): 1 VCC, 2 GND, 3 SCL, 4 SDA, 5 DC, 6 CS, 7 RST.",
                "J2 -> modulo (serigrafia del modulo): 1 VCC, 2 GND, 3 SCL, 4 SDA, 5 DC, 6 CS, 7 RST,\\n"
                "8 BUSY (solo e-paper, DEC-049; con il GC9A01 a 7 pin resta libero).")
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for x, y, rot, just in ((379.73, 127, 270, "right"), (140.97, 105.41, 180, "right")):
    m = re.search(r'\t\(label "IO1"\n\t\t\(at %s %s %d\)\n.*?\n\t\)\n' % (re.escape("%g" % x), re.escape("%g" % y), rot), t, re.S)
    assert m, (x, y)
    t = t.replace(m.group(0), global_label("DISP_BUSY", "%g" % x, "%g" % y, rot, just))
t = sostituisci(t, '"IO1 (libero)"', '"IO1 (DISP_BUSY)"')
open(MCU, "w", encoding="utf-8", newline="\n").write(t)

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                "header 8 pin 2,54 mm THT verso il modulo GC9A01 (VCC, GND, SCL, SDA, DC, CS, RST sui pin 1-7;\\n"
                "   pin 8 BUSY per un eventuale e-paper, DEC-049),")
t = sostituisci(t, "IO0, IO1 liberi su punti di test | IO2 I2C_SDA",
                "IO0 libero su TP9 | IO1 DISP_BUSY (J2 pin 8, TP10) | IO2 I2C_SDA")
open(ROOT, "w", encoding="utf-8", newline="\n").write(t)
# ------------------------------------------------------------------ libreria PoliClock: simbolo 1x8 (il 1x7 resta)
LIB = os.path.join(os.path.dirname(HERE), "lib", "PoliClock.kicad_sym")
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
